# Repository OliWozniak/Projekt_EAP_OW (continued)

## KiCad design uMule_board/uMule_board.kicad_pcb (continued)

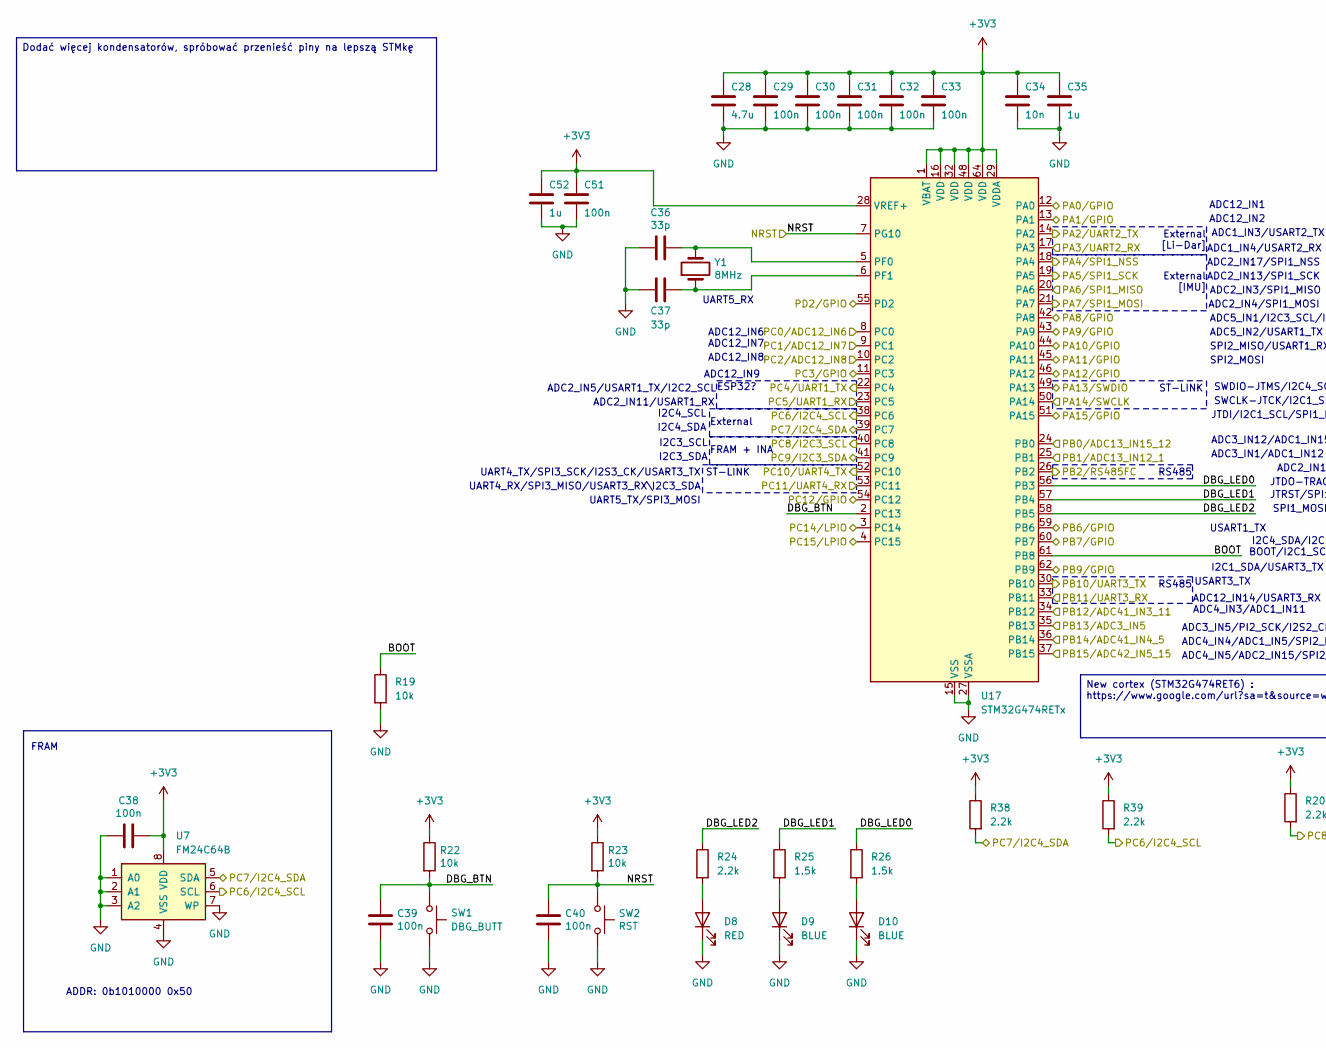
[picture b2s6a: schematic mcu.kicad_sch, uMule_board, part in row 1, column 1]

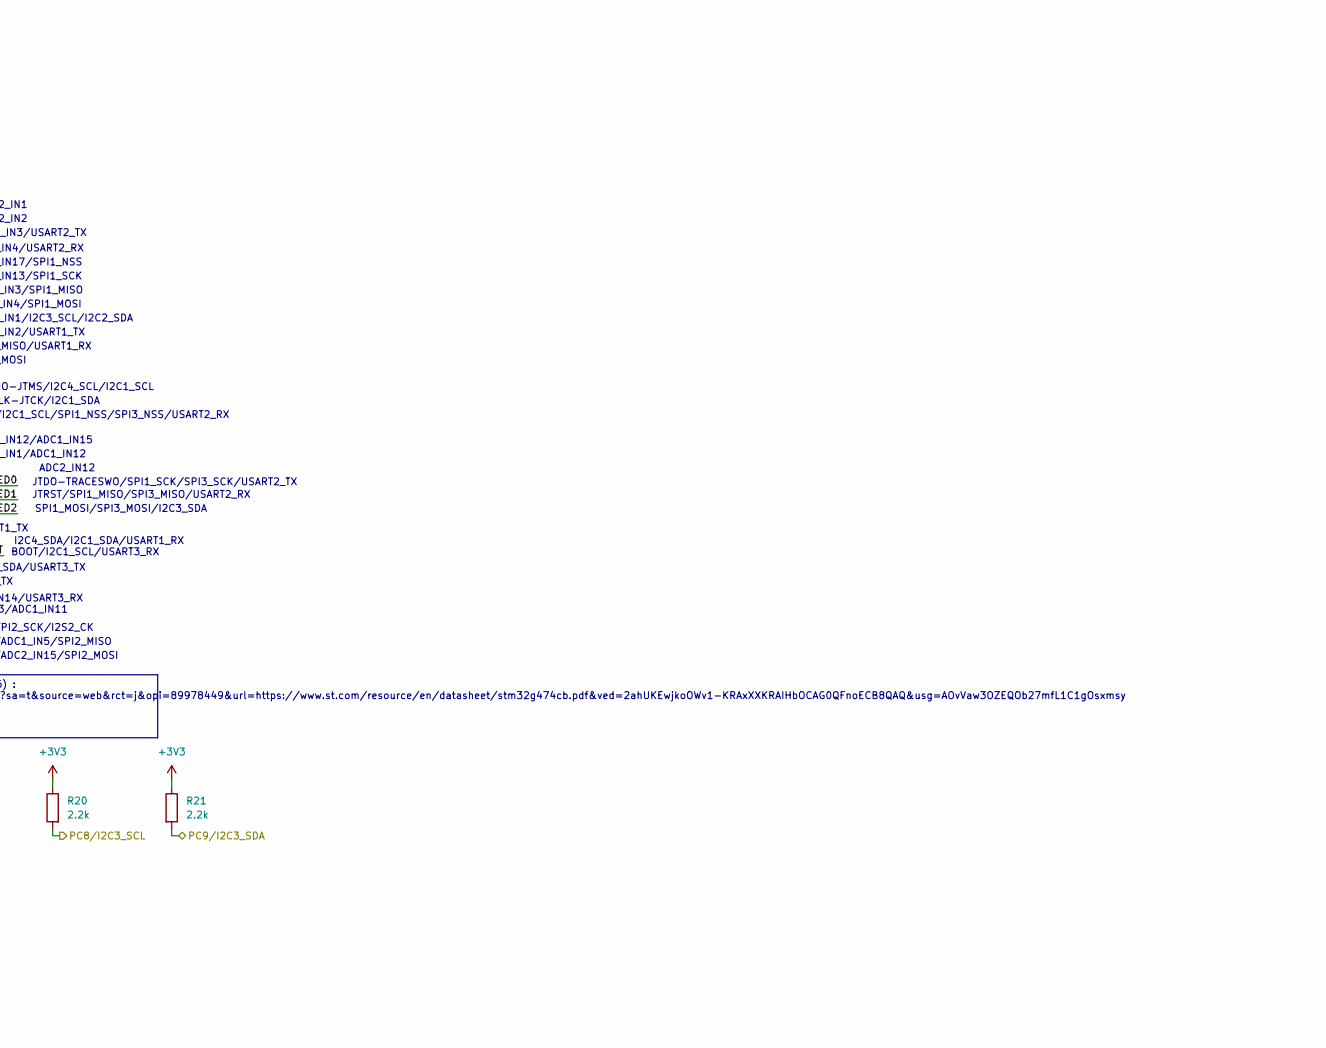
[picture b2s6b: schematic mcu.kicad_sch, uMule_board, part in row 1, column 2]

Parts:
C28: 4.7u; C_0603_1608Metric
C29, C30, C31, C32, C33, C38, C39, C40, C51: 100n; C_0603_1608Metric
C34: 10n; C_0603_1608Metric
C35, C52: 1u; C_0603_1608Metric
C36, C37: 33p; C_0603_1608Metric
D8: RED; LED_0603_1608Metric_Pad1.05x0.95mm_HandSolder
D9, D10: BLUE; LED_0603_1608Metric_Pad1.05x0.95mm_HandSolder
R19, R22, R23: 10k; R_0603_1608Metric
R20, R21, R24, R38, R39: 2.2k; R_0603_1608Metric
R25, R26: 1.5k; R_0603_1608Metric
SW1: DBG_BUTT; SW_SPST_TL3342
SW2: RST; SW_SPST_TL3342
U7: FM24C64B; SOIC-8_3.9x4.9mm_P1.27mm
U17: STM32G474RETx; LQFP-64_10x10mm_P0.5mm
Y1: 8MHz; Crystal_SMD_5032-2Pin_5.0x3.2mm

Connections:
+3V3: C28.1, C29.1, C30.1, C31.1, C32.1, C33.1, C34.1, C35.1, C38.1, C51.1, C52.1, R20.1, R21.1, R22.1, R23.1, R38.1, R39.1, U7.8 (VDD), U17.1 (VBAT), U17.16 (VDD), U17.28 (VREF+), U17.29 (VDDA), U17.32 (VDD), U17.48 (VDD), U17.64 (VDD); also elsewhere on the board
/Communication/CS: U17.18 (PA4); also elsewhere on the board
/Communication/ESP32_RX: U17.23 (PC5); also elsewhere on the board
/Communication/ESP32_TX: U17.22 (PC4); also elsewhere on the board
/Communication/I2C_SCL: R20.2, U17.40 (PC8); also elsewhere on the board
/Communication/I2C_SDA: R21.2, U17.41 (PC9); also elsewhere on the board
/Communication/Li-Dar_RX: U17.17 (PA3); also elsewhere on the board
/Communication/Li-Dar_TX: U17.14 (PA2); also elsewhere on the board
/Communication/RS485_DI: U17.30 (PB10); also elsewhere on the board
/Communication/RS485_FC: U17.26 (PB2); also elsewhere on the board
/Communication/RS485_RO: U17.33 (PB11); also elsewhere on the board
/Communication/SPI_MISO: U17.20 (PA6); also elsewhere on the board
/Communication/SPI_MOSI: U17.21 (PA7); also elsewhere on the board
/Communication/SPI_SCK: U17.19 (PA5); also elsewhere on the board
/Communication/SWCLK: U17.50 (PA14); also elsewhere on the board
/Communication/SWDIO: U17.49 (PA13); also elsewhere on the board
/Communication/VCP_RX: U17.53 (PC11); also elsewhere on the board
/Communication/VCP_TX: U17.52 (PC10); also elsewhere on the board
/GPIO/GPIO_0: U17.12 (PA0); also elsewhere on the board
/GPIO/GPIO_1: U17.13 (PA1); also elsewhere on the board
/GPIO/GPIO_2: U17.42 (PA8); also elsewhere on the board
/GPIO/GPIO_3: U17.43 (PA9); also elsewhere on the board
/GPIO/GPIO_4: U17.44 (PA10); also elsewhere on the board
/GPIO/GPIO_5: U17.45 (PA11); also elsewhere on the board
/GPIO/GPIO_6: U17.46 (PA12); also elsewhere on the board
/GPIO/GPIO_7: U17.51 (PA15); also elsewhere on the board
/GPIO/GPIO_8: U17.59 (PB6); also elsewhere on the board
/GPIO/GPIO_9: U17.60 (PB7); also elsewhere on the board
/GPIO/GPIO_10: U17.62 (PB9); also elsewhere on the board
/GPIO/GPIO_11: U17.11 (PC3); also elsewhere on the board
/GPIO/GPIO_12: U17.54 (PC12); also elsewhere on the board
/GPIO/GPIO_13: U17.3 (PC14); also elsewhere on the board
/GPIO/GPIO_14: U17.4 (PC15); also elsewhere on the board
/GPIO/GPIO_15: U17.55 (PD2); also elsewhere on the board
/MCU/BOOT: R19.1, U17.61 (PB8)
/MCU/DBG_BTN: C39.1, R22.2, SW1.1, U17.2 (PC13)
/MCU/DBG_LED0: R26.1, U17.56 (PB3)
/MCU/DBG_LED1: R25.1, U17.57 (PB4)
/MCU/DBG_LED2: R24.1, U17.58 (PB5)
/MCU/NRST: C40.1, R23.2, SW2.1, U17.7 (PG10); also elsewhere on the board
/MCU/PC6/I2C4_SCL: R39.2, U7.6 (SCL), U17.38 (PC6); also elsewhere on the board
/MCU/PC7/I2C4_SDA: R38.2, U7.5 (SDA), U17.39 (PC7); also elsewhere on the board
/Photodiodes/PHO_0: U17.37 (PB15); also elsewhere on the board
/Photodiodes/PHO_1: U17.36 (PB14); also elsewhere on the board
/Photodiodes/PHO_2: U17.34 (PB12); also elsewhere on the board
/Photodiodes/PHO_3: U17.25 (PB1); also elsewhere on the board
/Photodiodes/PHO_4: U17.24 (PB0); also elsewhere on the board
/Photodiodes/PHO_5: U17.10 (PC2); also elsewhere on the board
/Photodiodes/PHO_6: U17.9 (PC1); also elsewhere on the board
/Photodiodes/PHO_7: U17.8 (PC0); also elsewhere on the board
/Photodiodes/V_{REF}: U17.35 (PB13); also elsewhere on the board
GND: C28.2, C29.2, C30.2, C31.2, C32.2, C33.2, C34.2, C35.2, C36.2, C37.2, C38.2, C39.2, C40.2, C51.2, C52.2, D8.1 (K), D9.1 (K), D10.1 (K), R19.2, SW1.2, SW2.2, U7.1 (A0), U7.2 (A1), U7.3 (A2), U7.4 (VSS), U7.7 (WP), U17.15 (VSS), U17.27 (VSSA), U17.31 (VSS), U17.47 (VSS), U17.63 (VSS); also elsewhere on the board
unnamed: D8.2 (A), R24.2
unnamed: D9.2 (A), R25.2
unnamed: D10.2 (A), R26.2
unnamed: C36.1, U17.5 (PF0), Y1.2
unnamed: C37.1, U17.6 (PF1), Y1.1

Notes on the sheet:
SWCLK-JTCK/I2C1_SDA
ST-LINK
UART4_RX/SPI3_MISO/USART3_RX\I2C3_SDA
SPI2_MOSI
ADC12_IN1
External
RS485
ADC2_IN11/USART1_RX
SPI1_MOSI/SPI3_MOSI/I2C3_SDA
ADC4_IN3/ADC1_IN11
JTDI/I2C1_SCL/SPI1_NSS/SPI3_NSS/USART2_RX
ADC5_IN1/I2C3_SCL/I2C2_SDA
USART1_TX
BOOT/I2C1_SCL/USART3_RX
ADC1_IN3/USART2_TX
ADC5_IN2/USART1_TX
I2C3_SCL
UART5_TX/SPI3_MOSI
External [Li-Dar]
ADC3_IN12/ADC1_IN15
ADDR: 0b1010000 0x50
ADC12_IN9
ADC2_IN12
ADC12_IN8
ADC1_IN4/USART2_RX
FRAM + INA
I2C4_SDA
USART3_TX
ADC2_IN5/USART1_TX/I2C2_SCL
ADC2_IN4/SPI1_MOSI
ADC12_IN2
I2C3_SDA
ADC12_IN14/USART3_RX
ADC12_IN6
UART5_RX
I2C4_SCL
I2C4_SDA/I2C1_SDA/USART1_RX
ADC2_IN3/SPI1_MISO
ADC2_IN17/SPI1_NSS
SWDIO-JTMS/I2C4_SCL/I2C1_SCL

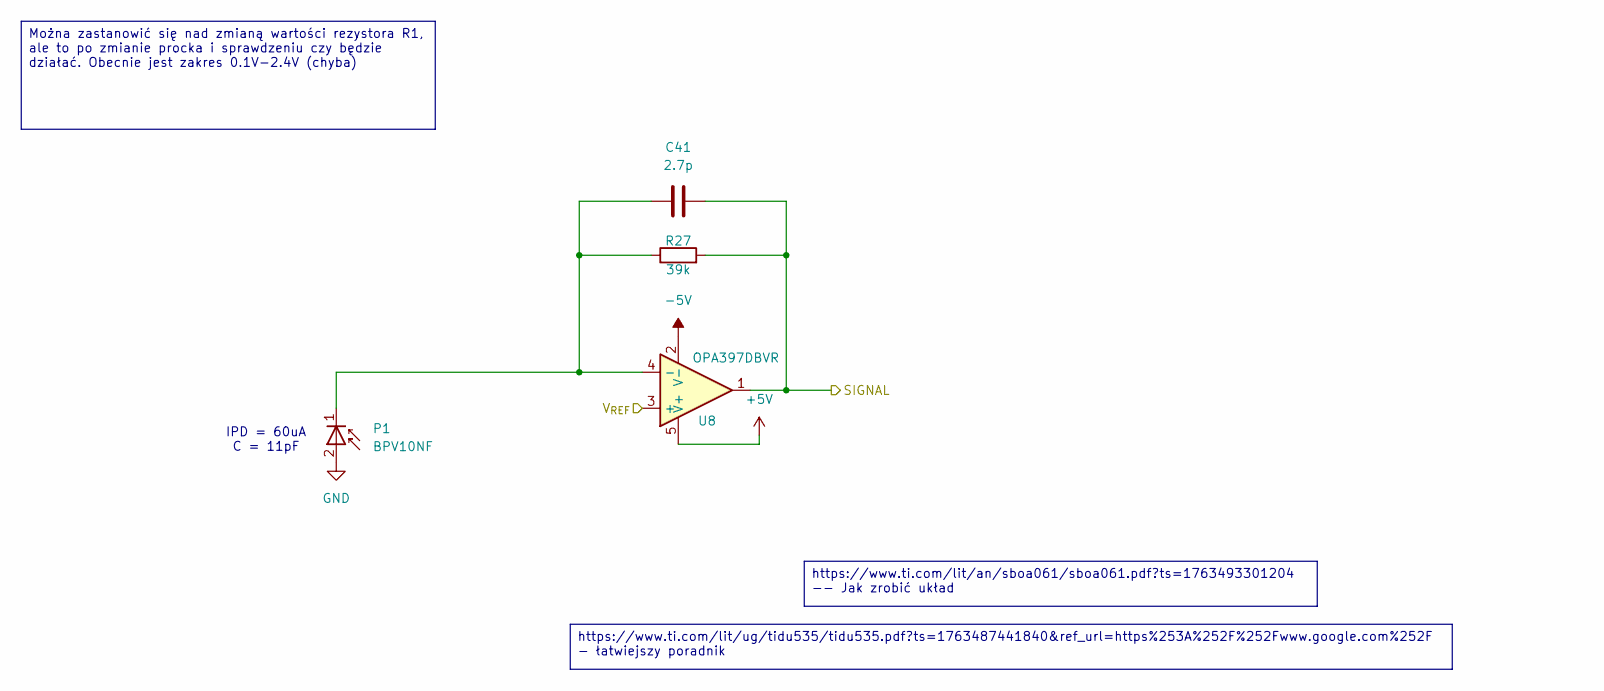
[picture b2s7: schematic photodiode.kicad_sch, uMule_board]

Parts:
C41: 2.7p; C_0402_1005Metric
P1: BPV10NF; D_T-1_P2.54mm_Vertical_KathodeUp
R27: 39k; R_0603_1608Metric
U8: OPA397DBVR; SOT-23-5

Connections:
+5V: U8.5 (V+); also elsewhere on the board
-5V: U8.2 (V-); also elsewhere on the board
/Photodiodes/PHO_0: C41.2, R27.2, U8.1; also elsewhere on the board
/Photodiodes/V_{REF}: U8.3 (+); also elsewhere on the board
GND: P1.2 (A); also elsewhere on the board
unnamed: C41.1, P1.1 (K), R27.1, U8.4 (-)

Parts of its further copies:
C42, C43, C44, C45, C46, C47, C48: 2.7p; C_0402_1005Metric
P2, P3, P4, P5, P6, P7, P8: BPV10NF; D_T-1_P2.54mm_Vertical_KathodeUp
R28, R29, R30, R31, R32, R33, R34: 39k; R_0603_1608Metric
U9, U10, U11, U12, U13, U14, U15: OPA397DBVR; SOT-23-5

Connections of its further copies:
+5V: U9.5 (V+), U10.5 (V+), U11.5 (V+), U12.5 (V+), U13.5 (V+), U14.5 (V+), U15.5 (V+); also elsewhere on the board
-5V: U9.2 (V-), U10.2 (V-), U11.2 (V-), U12.2 (V-), U13.2 (V-), U14.2 (V-), U15.2 (V-); also elsewhere on the board
/Photodiodes/PHO_1: C42.2, R28.2, U9.1; also elsewhere on the board
/Photodiodes/PHO_2: C43.2, R29.2, U10.1; also elsewhere on the board
/Photodiodes/PHO_3: C44.2, R30.2, U11.1; also elsewhere on the board
/Photodiodes/PHO_4: C45.2, R31.2, U12.1; also elsewhere on the board
/Photodiodes/PHO_5: C46.2, R32.2, U13.1; also elsewhere on the board
/Photodiodes/PHO_6: C47.2, R33.2, U14.1; also elsewhere on the board
/Photodiodes/PHO_7: C48.2, R34.2, U15.1; also elsewhere on the board
/Photodiodes/V_{REF}: U9.3 (+), U10.3 (+), U11.3 (+), U12.3 (+), U13.3 (+), U14.3 (+), U15.3 (+); also elsewhere on the board
GND: P2.2 (A), P3.2 (A), P4.2 (A), P5.2 (A), P6.2 (A), P7.2 (A), P8.2 (A); also elsewhere on the board
unnamed: C42.1, P2.1 (K), R28.1, U9.4 (-)
unnamed: C43.1, P3.1 (K), R29.1, U10.4 (-)
unnamed: C44.1, P4.1 (K), R30.1, U11.4 (-)
unnamed: C45.1, P5.1 (K), R31.1, U12.4 (-)
unnamed: C46.1, P6.1 (K), R32.1, U13.4 (-)
unnamed: C47.1, P7.1 (K), R33.1, U14.4 (-)
unnamed: C48.1, P8.1 (K), R34.1, U15.4 (-)

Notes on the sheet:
IPD = 60uA C = 11pF
https://www.ti.com/lit/ug/tidu535/tidu535.pdf?ts=1763487441840&ref_url=https%253A%252F%252Fwww.google.com%252F - łatwiejszy poradnik
https://www.ti.com/lit/an/sboa061/sboa061.pdf?ts=1763493301204 -- Jak zrobić układ
Można zastanowić się nad zmianą wartości rezystora R1, ale to po zmianie procka i sprawdzeniu czy będzie działać. Obecnie jest zakres 0.1V-2.4V (chyba)

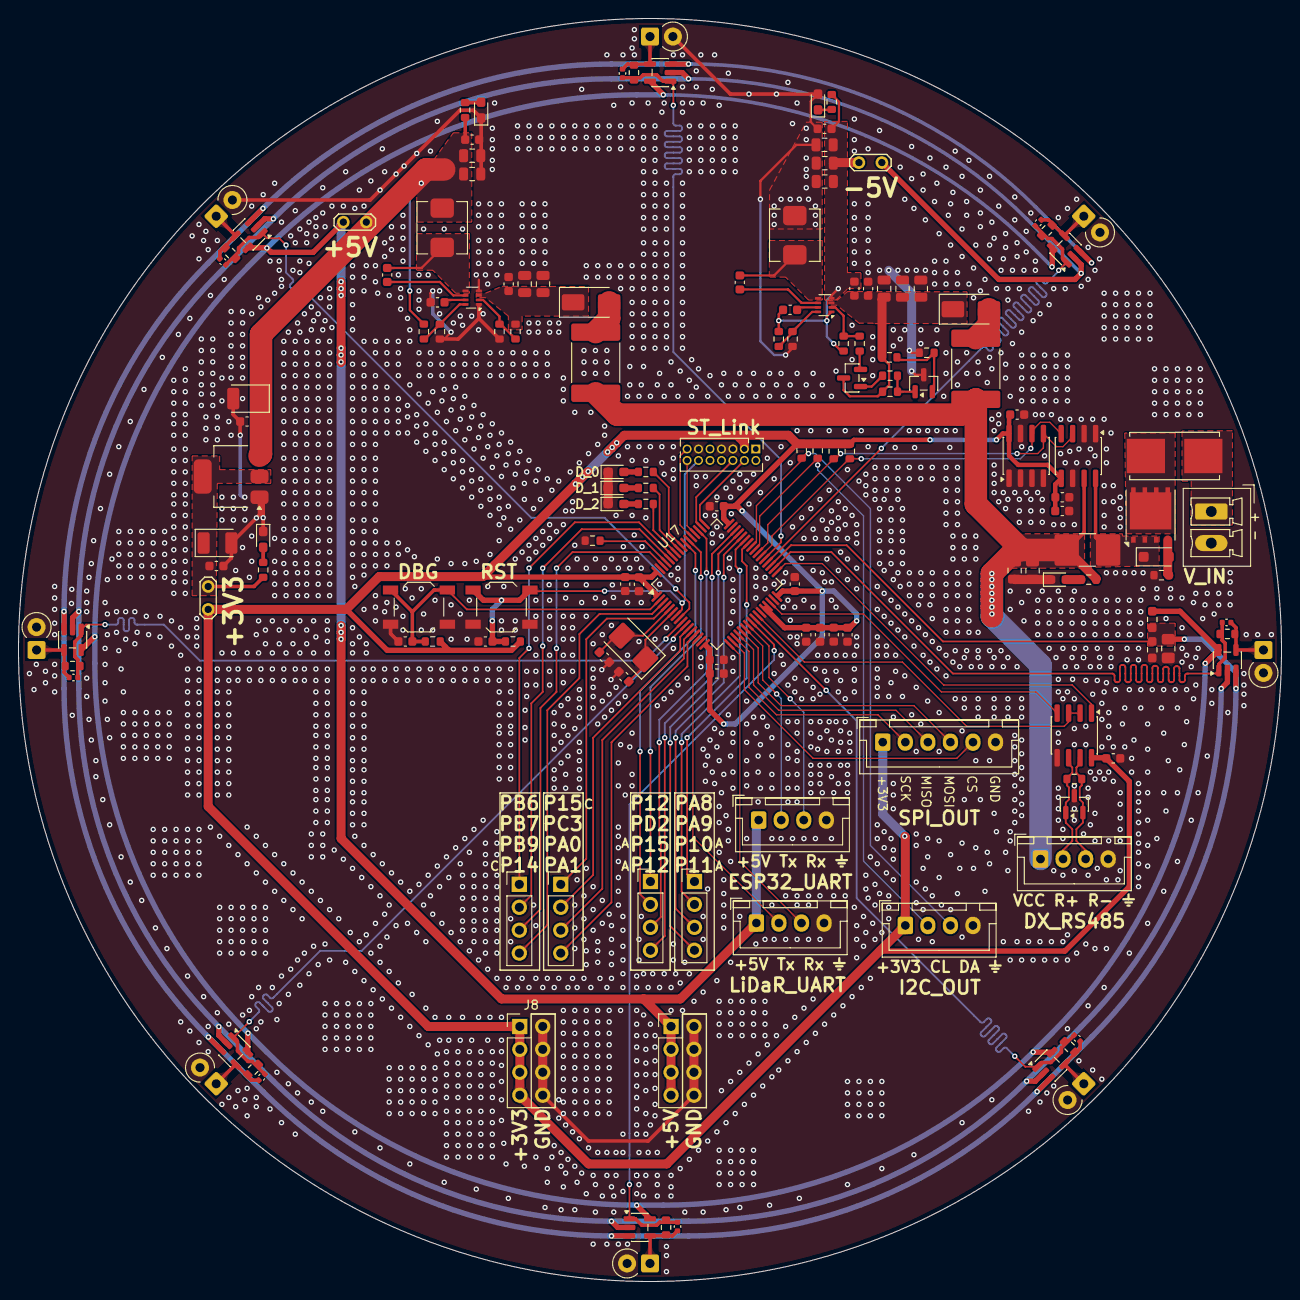
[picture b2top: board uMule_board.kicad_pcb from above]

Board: 2 copper layers, 140.0 x 140.0 mm, 152 parts (0 on the bottom side), 99 nets.

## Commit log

2025-12-03 added notes for development
2025-12-03 addd buses and simple connections
2025-12-04 Some calculations were made. Photodiode, amplifier and main procesor are chosen
2025-12-06 all main componenst added. Prepared to change MCU. SCH almost ready
2025-12-13 Finished schematics. Now ready for PCB
2025-12-14 Started working on PCB. Ditched high power outputs. Focusing on photodiodes. One commit closer to order
2025-12-14 modified pdf files
2025-12-20 removed half phototransistors, etc.
2025-12-21 sch ready, only missing the pcb
2025-12-23 board before I place photodides
2025-12-24 after placing photodiodes
2025-12-25 placed uC, initial traces connection, Matrzed trases lenghts for photodiodes (idk why)
2025-12-25 another day, more progress. Elements are placed on board, traces need to be conected, added jumpers for power in case of bad design
2025-12-28 DRC Passed, now only slight modifications on traces left, lenght matching and proper board description
2025-12-28 Added descriptions and teardrops. Ready for JLCPCB
2025-12-29 initial commit for new processor. Need to adjust pinout and layout of board. Try not to change elements names to save DC converters and photodiodes layout
2025-12-31 Described pinout. Board seems viable
2025-12-31 initial board is ready for conecting
2025-12-31 Added drawings
2026-01-02 All elements connected. Now making more vias and corrections
2026-01-04 Board finished, ready to order
2026-01-05 Commit for transmitter board. Oscillator is calculated and circuit is made. I should make simulations before completing board but circuit is foolproof. Quadrature oscillator will be used as it provid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
2026-01-06 Transmiter board finnished. Ready for JLCPCB
2026-01-06 JLC Ready, now waiting for shipment
2026-01-27 current board. Everything is finnished
2026-05-02 added 3d model
